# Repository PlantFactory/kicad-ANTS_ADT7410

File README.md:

# kicad-ANTS_ADT7410

ANTS ADT7420 dry/wet temperature sensor compatible board using ADT7410.
Moreover, panelized version is available (including SHT31 board).

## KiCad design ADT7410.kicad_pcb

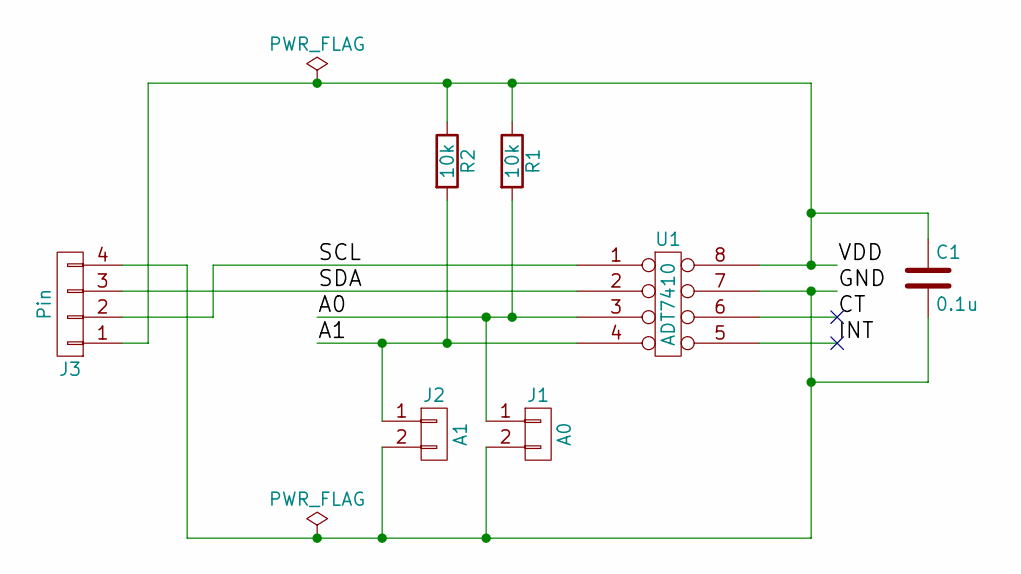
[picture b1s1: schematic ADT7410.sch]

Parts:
C1: 0.1u; C_0603_HandSoldering
J1: A0; Pin_Header_Straight_1x02_Pitch1.27mm
J2: A1; Pin_Header_Straight_1x02_Pitch1.27mm
J3: Pin; Pin_Header_Straight_1x04_Pitch1.27mm
R1, R2: 10k; R_0603_HandSoldering
U1: ADT7410; SOIC-8-N

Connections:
/A0: J1.1, R1.2, U1.3
/A1: J2.1, R2.2, U1.4
/CT: U1.6
/GND: C1.2, J1.2, J2.2, J3.4, U1.7
/INT: U1.5
/SCL: J3.2, U1.1
/SDA: J3.3, U1.2
/VDD: C1.1, J3.1, R1.1, R2.1, U1.8

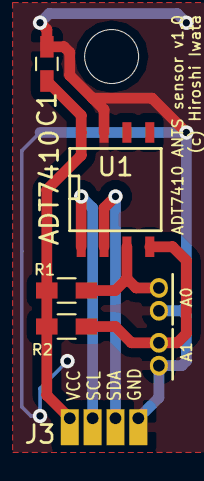
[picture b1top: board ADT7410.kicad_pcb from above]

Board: 2 copper layers, 8 parts (0 on the bottom side), 6 nets.

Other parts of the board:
H1: VIA_M3
